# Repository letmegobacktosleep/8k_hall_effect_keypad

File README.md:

8 key hall effect pcb using STM32F072CBT6
- has not been tested
- requires [JLCPCB Tools](https://github.com/Bouni/kicad-jlcpcb-tools) plugin for exporting gerbers/bom/pos

untested firmware available at https://github.com/letmegobacktosleep/qmk_firmware/tree/minipad

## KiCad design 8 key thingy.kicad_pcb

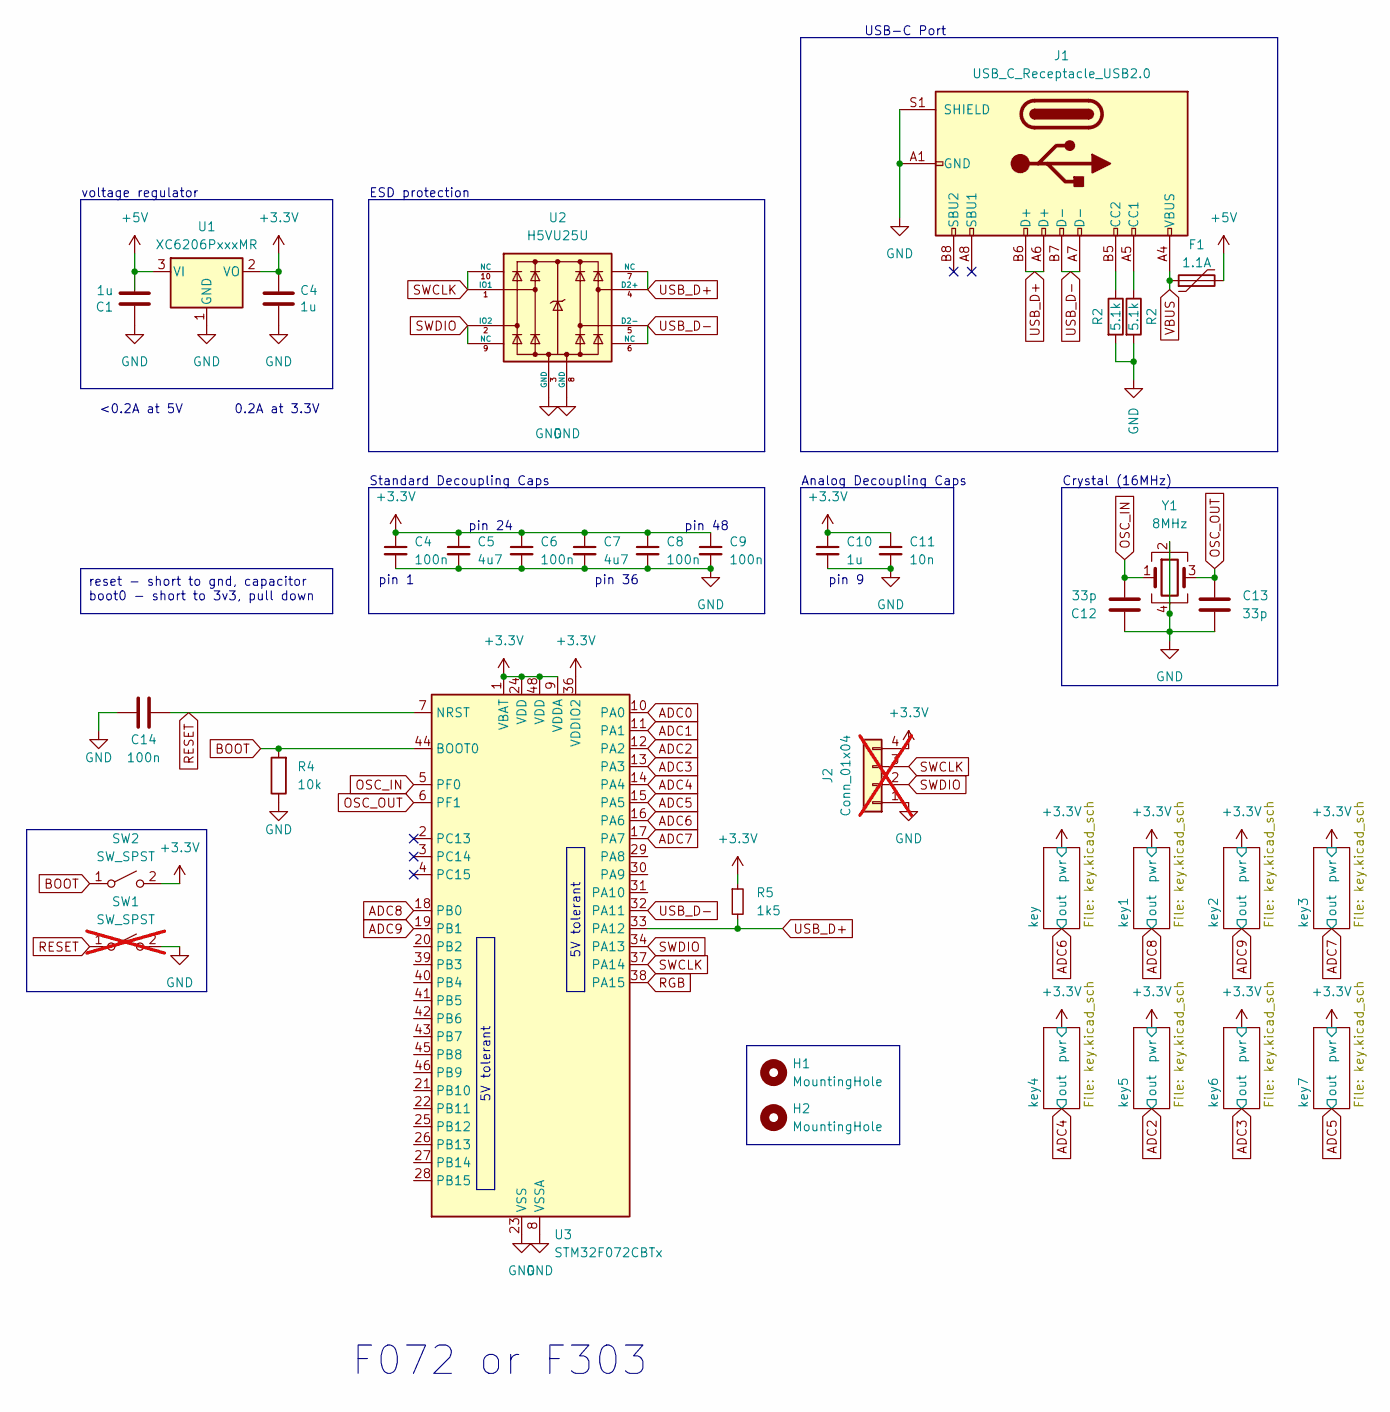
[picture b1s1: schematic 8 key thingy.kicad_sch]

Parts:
C1, C4: 1u; C_0805_2012Metric; LCSC C28323
C5, C7: 4u7; C_0402_1005Metric; LCSC C23733
C6, C8, C9, C14: 100n; C_0402_1005Metric; LCSC C1525
C10: 1u; C_0402_1005Metric; LCSC C52923
C11: 10n; C_0402_1005Metric; LCSC C15195
C12, C13: 33p; C_0402_1005Metric; LCSC C1562
F1: 1.1A; Fuse_1206_3216Metric; LCSC C2760273
H1, H2: MountingHole; MountingHole_3.2mm_M3
J1: USB_C_Receptacle_USB2.0; USB_C_Receptacle_HRO_TYPE-C-31-M-12 (marbastlib); LCSC C165948
J2: Conn_01x04; PinSocket_1x04_P2.54mm_Vertical; not fitted
R2: 5.1k; R_0402_1005Metric; LCSC C25905
R4: 10k; R_0402_1005Metric; LCSC C25744
R5: 1k5; R_0603_1608Metric; LCSC C22843
SW1: SW_SPST; SW_SPST_TL3342; LCSC C318884; not fitted
SW2: SW_SPST; SW_SPST_TL3342; LCSC C318884
U1: XC6206PxxxMR; SOT-23; LCSC C5446
U2: H5VU25U; DFN2510 (from moonboard); Manufacturer Part Number TPD4E05U06DQAR; LCSC Part Number C7420374
U3: STM32F072CBTx; LQFP-48_7x7mm_P0.5mm; LCSC C81720
Y1: 8MHz; Crystal_SMD_3225-4Pin_3.2x2.5mm; LCSC C2682774

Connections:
+3.3V: C4.1, C5.1, C6.1, C7.1, C8.1, C9.1, C10.1, C11.1, J2.4, R5.1, SW2.2 (B), U1.2 (VO), U3.1 (VBAT), U3.9 (VDDA), U3.24 (VDD), U3.36 (VDDIO2), U3.48 (VDD); also elsewhere on the board
+5V: F1.2, U1.3 (VI); also elsewhere on the board
ADC0: U3.10 (PA0)
ADC1: U3.11 (PA1)
ADC2: U3.12 (PA2); also elsewhere on the board
ADC3: U3.13 (PA3); also elsewhere on the board
ADC4: U3.14 (PA4); also elsewhere on the board
ADC5: U3.15 (PA5); also elsewhere on the board
ADC6: U3.16 (PA6); also elsewhere on the board
ADC7: U3.17 (PA7); also elsewhere on the board
ADC8: U3.18 (PB0); also elsewhere on the board
ADC9: U3.19 (PB1); also elsewhere on the board
BOOT: R4.2, SW2.1 (A), U3.44 (BOOT0)
GND: C4.2, C5.2, C6.2, C7.2, C8.2, C9.2, C10.2, C11.2, C12.1, C13.2, C14.2, J1.A1 (GND), J1.A12 (GND), J1.B1 (GND), J1.B12 (GND), J1.S1 (SHIELD), J2.1, R2.2, R4.1, U1.1 (GND), U2.3 (GND), U2.8 (GND), U3.8 (VSSA), U3.23 (VSS), U3.35 (VSS), U3.47 (VSS), Y1.2, Y1.4; also elsewhere on the board
OSC_IN: C12.2, U3.5 (PF0), Y1.1
OSC_OUT: C13.1, U3.6 (PF1), Y1.3
RESET: C14.1, SW1.1 (A), U1.7, U3.7 (NRST)
RGB: U3.38 (PA15)
SWCLK: J2.3, U2.1 (IO1), U2.10 (NC), U3.37 (PA14)
SWDIO: J2.2, U2.2 (IO2), U2.9 (NC), U3.34 (PA13)
USB_D+: J1.A6 (D+), J1.B6 (D+), R5.2, U2.4 (D2+), U2.7 (NC), U3.33 (PA12)
USB_D-: J1.A7 (D-), J1.B7 (D-), U2.5 (D2-), U2.6 (NC), U3.32 (PA11)
VBUS: F1.1, J1.A4 (VBUS), J1.A9 (VBUS), J1.B4 (VBUS), J1.B9 (VBUS)

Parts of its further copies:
C2, C3: 1u; C_0805_2012Metric; LCSC C28323
R3: 5.1k; R_0402_1005Metric; LCSC C25905

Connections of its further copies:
+3.3V: C3.1; also elsewhere on the board
+5V: C2.2; also elsewhere on the board
GND: C2.1, C3.2, R3.2; also elsewhere on the board

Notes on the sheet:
5V tolerant
reset - short to gnd, capacitor boot0 - short to 3v3, pull down
F072 or F303
Analog Decoupling Caps
pin 48
ESD protection
Standard Decoupling Caps
0.2A at 3.3V
USB-C Port
voltage regulator
pin 36
pin 24
Crystal (16MHz)
pin 9
<0.2A at 5V
pin 1

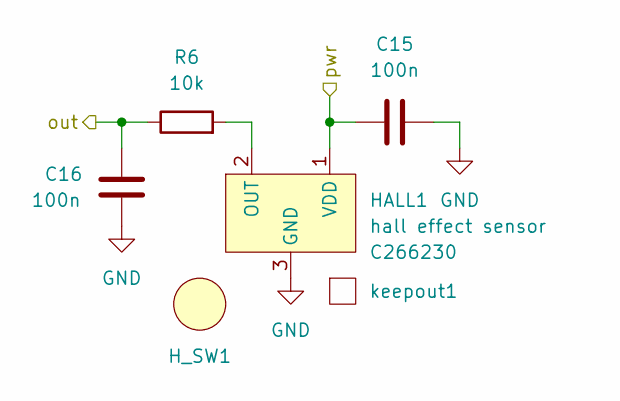
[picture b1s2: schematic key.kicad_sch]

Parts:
C15, C16: 100n; C_0402_1005Metric; LCSC C1525
HALL1: hall effect sensor; SOT-23; LCSC C266230
H_SW1: switch holes; LCSC holes
R6: 10k; R_0402_1005Metric; LCSC C25744
keepout1: copper_keepout

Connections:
+3.3V: C15.1, HALL1.1 (VDD); also elsewhere on the board
ADC6: C16.2, R6.1; also elsewhere on the board
GND: C15.2, C16.1, HALL1.3 (GND); also elsewhere on the board
unnamed: HALL1.2 (OUT), R6.2

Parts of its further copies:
C17, C18, C19, C20, C21, C22, C23, C24, C25, C26, C27, C28, C29, C30: 100n; C_0402_1005Metric; LCSC C1525
HALL2, HALL3, HALL4, HALL5, HALL6, HALL7, HALL8: hall effect sensor; SOT-23; LCSC C266230
H_SW2, H_SW3, H_SW4, H_SW5, H_SW6, H_SW7, H_SW8: switch holes; LCSC holes
R7, R8, R9, R10, R11, R12, R13: 10k; R_0402_1005Metric; LCSC C25744
keepout2, keepout3, keepout4, keepout5, keepout6, keepout7, keepout8: copper_keepout

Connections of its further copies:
+3.3V: C17.1, C19.1, C21.1, C23.1, C25.1, C27.1, C29.1, HALL2.1 (VDD), HALL3.1 (VDD), HALL4.1 (VDD), HALL5.1 (VDD), HALL6.1 (VDD), HALL7.1 (VDD), HALL8.1 (VDD); also elsewhere on the board
ADC2: C26.2, R11.1; also elsewhere on the board
ADC3: C28.2, R12.1; also elsewhere on the board
ADC4: C24.2, R10.1; also elsewhere on the board
ADC5: C30.2, R13.1; also elsewhere on the board
ADC7: C22.2, R9.1; also elsewhere on the board
ADC8: C18.2, R7.1; also elsewhere on the board
ADC9: C20.2, R8.1; also elsewhere on the board
GND: C17.2, C18.1, C19.2, C20.1, C21.2, C22.1, C23.2, C24.1, C25.2, C26.1, C27.2, C28.1, C29.2, C30.1, HALL2.3 (GND), HALL3.3 (GND), HALL4.3 (GND), HALL5.3 (GND), HALL6.3 (GND), HALL7.3 (GND), HALL8.3 (GND); also elsewhere on the board
unnamed: HALL2.2 (OUT), R7.2
unnamed: HALL3.2 (OUT), R8.2
unnamed: HALL4.2 (OUT), R9.2
unnamed: HALL5.2 (OUT), R10.2
unnamed: HALL6.2 (OUT), R11.2
unnamed: HALL7.2 (OUT), R12.2
unnamed: HALL8.2 (OUT), R13.2

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
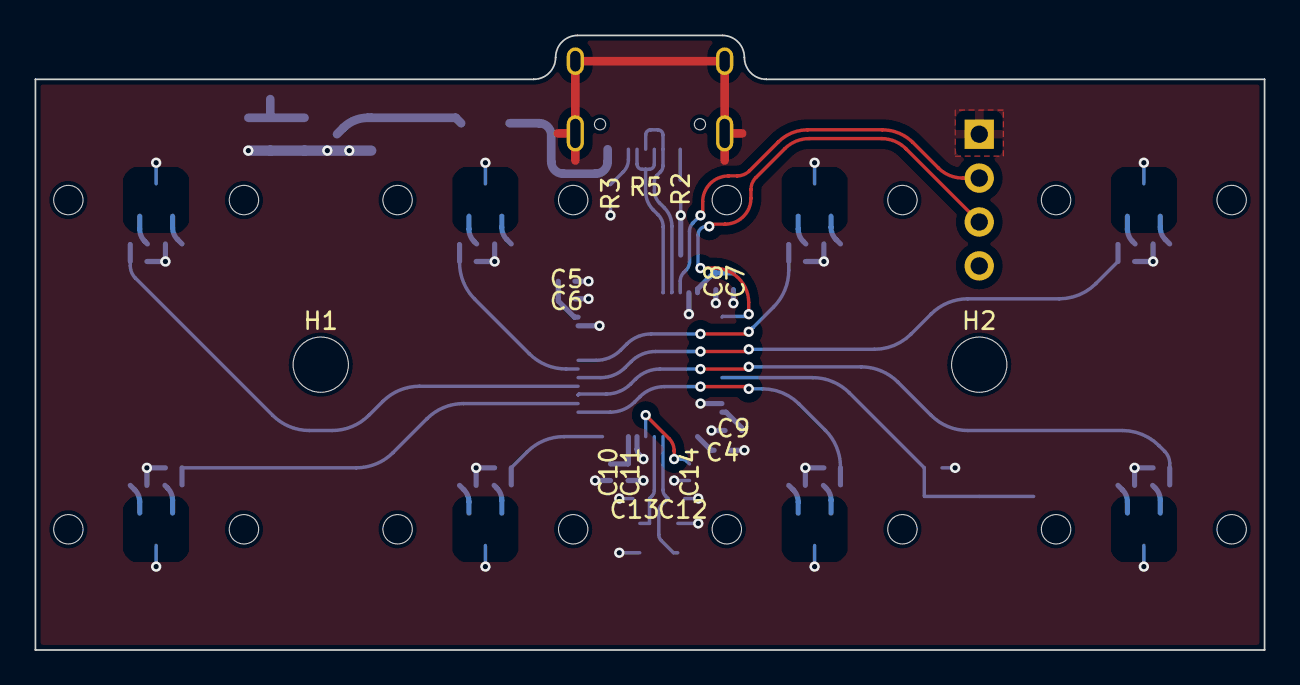
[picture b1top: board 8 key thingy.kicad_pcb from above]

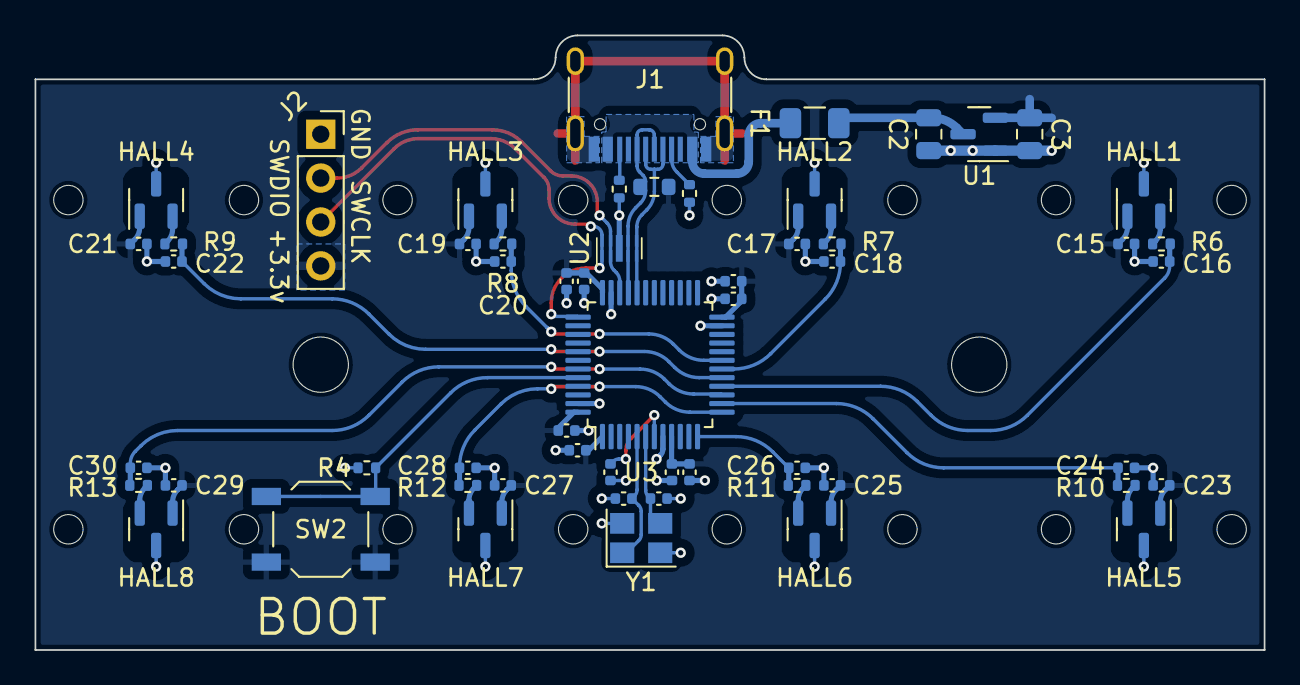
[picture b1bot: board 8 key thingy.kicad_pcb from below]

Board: 2 copper layers, 71.1 x 35.6 mm, 75 parts (65 on the bottom side), 30 nets.

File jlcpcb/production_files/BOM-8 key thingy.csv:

Comment,Designator,Footprint,LCSC
10n,C11,C_0402_1005Metric,C15195
100n,"C14,C15,C16,C17,C18,C19,C20,C21,C22,C23,C24,C25,C26,C27,C28,C29,C30,C4,C6,C8,C9",C_0402_1005Metric,C1525
33p,"C12,C13",C_0402_1005Metric,C1562
USB_C_Receptacle_USB2.0,J1,USB_C_Receptacle_HRO_TYPE-C-31-M-12 (marbastlib),C165948
4u7,"C5,C7",C_0402_1005Metric,C23733
10k,"R10,R11,R12,R13,R4,R6,R7,R8,R9",R_0402_1005Metric,C25744
1k5,R5,R_0402_1005Metric,C25867
5.1k,"R2,R3",R_0402_1005Metric,C25905
hall effect sensor,"HALL1,HALL2,HALL3,HALL4,HALL5,HALL6,HALL7,HALL8",SOT-23,C266230
8MHz,Y1,Crystal_SMD_3225-4Pin_3.2x2.5mm,C2682774
1.1A,F1,Fuse_1206_3216Metric,C2760273
1u,"C2,C3",C_0805_2012Metric,C28323
SW_SPST,SW2,SW_SPST_TL3342,C318884
1u,C10,C_0402_1005Metric,C52923
XC6206PxxxMR,U1,SOT-23,C5446
H5VU25U,U2,DFN2510 (from moonboard),C7420374
STM32F072CBTx,U3,LQFP-48_7x7mm_P0.5mm,C81720

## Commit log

2024-04-30 new repository first upload
